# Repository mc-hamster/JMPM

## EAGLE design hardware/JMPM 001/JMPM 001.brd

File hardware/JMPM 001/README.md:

Sent to JLC PCB on May 7, 2020

Distributor part numbers for LCSC are included as an attribute on every component.

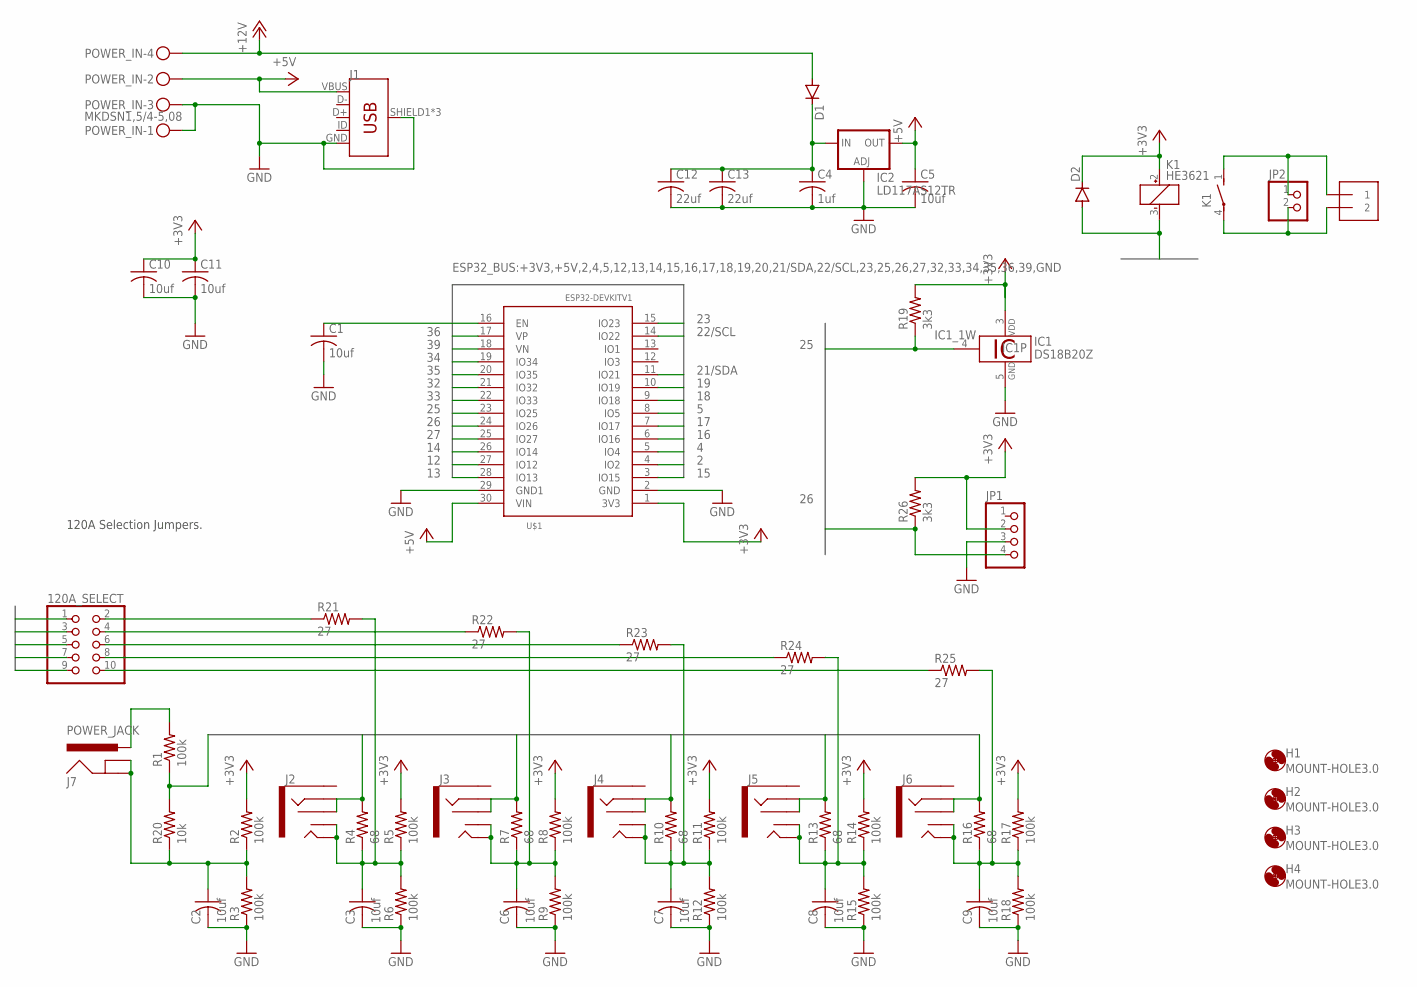
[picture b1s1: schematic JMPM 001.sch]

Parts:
120A_SELECT: PINHD-2X5; 2X05
C1, C2, C3, C5, C6, C7, C8, C9, C10, C11: 10uf; C0603; LCSC_PART_NUMBER C19702
C4: 1uf; C0603; LCSC_PART_NUMBER C15849
C12, C13: 22uf; C0805; LCSC_PART_NUMBER C45783
D1, D2: DIODE-DO-214AC; DO-214AC; LCSC_PART_NUMBER C95872
H1, H2, H3, H4: MOUNT-HOLE3.0; 3,0
IC1: DS18B20Z; SO08; LCSC_PART_NUMBER C97190
IC2: LD117AS12TR; SOT223; LCSC_PART_NUMBER C6187
J1: USB_MICRO-BREDUCED_PASTE; USB-B-MICRO-SMD_RED_PASTE
J2, J3, J4, J5, J6: AUDIO_JACK_3.5MM_KIT; AUDIO-JACK-KIT
J7: POWER_JACK; POWER_JACK_PTH
JP1: PINHD-1X4/90; 1X04/90
JP2: PINHD-1X2; 1X02
JP2B: 1X2-3.5MM; MPN OSTTE020161
K1: HE3621; MPN HE3621A0510
POWER_IN: MKDSN1,5/4-5,08
R1, R2, R3, R5, R6, R8, R9, R11, R12, R14, R15, R17, R18: 100k; R0603; LCSC_PART_NUMBER C25803
R4, R7, R10, R13, R16: 68; R0603; LCSC_PART_NUMBER C27592
R19, R26: 3k3; R0603; LCSC_PART_NUMBER C22978
R20: 10k; R0603; LCSC_PART_NUMBER C25804
R21, R22, R23, R24, R25: 27; R0603; LCSC_PART_NUMBER C25190
U$1: ESP32DEVKITV1; ESP32-DEVKITV1

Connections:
2: U$1.4 (IO2)
4: U$1.5 (IO4)
5: U$1.8 (IO5)
12: U$1.27 (IO12)
13: U$1.28 (IO13)
14: U$1.26 (IO14)
15: U$1.3 (IO15)
16: U$1.6 (IO16)
17: U$1.7 (IO17)
18: U$1.9 (IO18)
19: U$1.10 (IO19)
21/SDA: U$1.11 (IO21)
22/SCL: U$1.14 (IO22)
23: U$1.15 (IO23)
25: IC1.4 (1W), R19.1, U$1.23 (IO25)
26: JP1.4, R26.1, U$1.24 (IO26)
27: D2.A, K1.3 (-), U$1.25 (IO27)
32: 120A_SELECT.7, J5.RING, J5.RSH, R13.2, U$1.21 (IO32)
33: 120A_SELECT.9, J6.RING, J6.RSH, R16.2, U$1.22 (IO33)
34: 120A_SELECT.3, J3.RING, J3.RSH, R7.2, U$1.19 (IO34)
35: 120A_SELECT.5, J4.RING, J4.RSH, R10.2, U$1.20 (IO35)
36: R1.1, R20.2, U$1.17 (VP)
39: 120A_SELECT.1, J2.RING, J2.RSH, R4.2, U$1.18 (VN)
+3V3: C10.1, C11.1, D2.C, IC1.3 (VDD), JP1.2, K1.2 (+), R2.2, R5.2, R8.2, R11.2, R14.2, R17.2, R19.2, R26.2, U$1.1 (3V3)
+5V: C5.1, IC2.4 (OUT), J1.VBUS, POWER_IN.2, U$1.30 (VIN)
+12V: D1.A, POWER_IN.4
GND: C1.2, C2.2, C3.2, C4.2, C5.2, C6.2, C7.2, C8.2, C9.2, C10.2, C11.2, C12.2, C13.2, IC1.5 (GND), IC2.1 (ADJ), J1.GND, J1.SHIELD1 (SHIELD), J1.SHIELD2 (SHIELD), J1.SHIELD3 (SHIELD), JP1.3, POWER_IN.1, POWER_IN.3, R3.1, R6.1, R9.1, R12.1, R15.1, R18.1, U$1.2 (GND), U$1.29 (GND1)
unnamed: C1.1, U$1.16 (EN)
unnamed: C4.1, C12.1, C13.1, D1.C, IC2.3 (IN)
unnamed: J7.PWR, R1.2
unnamed: JP2.1, JP2B.1, K1.1 (S)
unnamed: 120A_SELECT.2, R21.1
unnamed: C2.1, J7.GND, J7.GNDBREAK, R2.1, R3.2, R20.1
unnamed: 120A_SELECT.4, R22.1
unnamed: C6.1, J3.TIP, J3.TSH, R7.1, R8.1, R9.2, R22.2
unnamed: 120A_SELECT.6, R23.1
unnamed: C7.1, J4.TIP, J4.TSH, R10.1, R11.1, R12.2, R23.2
unnamed: 120A_SELECT.8, R24.1
unnamed: C8.1, J5.TIP, J5.TSH, R13.1, R14.1, R15.2, R24.2
unnamed: 120A_SELECT.10, R25.1
unnamed: C9.1, J6.TIP, J6.TSH, R16.1, R17.1, R18.2, R25.2
unnamed: C3.1, J2.TIP, J2.TSH, R4.1, R5.1, R6.2, R21.2
unnamed: JP2.2, JP2B.2, K1.4

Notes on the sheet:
120A Selection Jumpers.

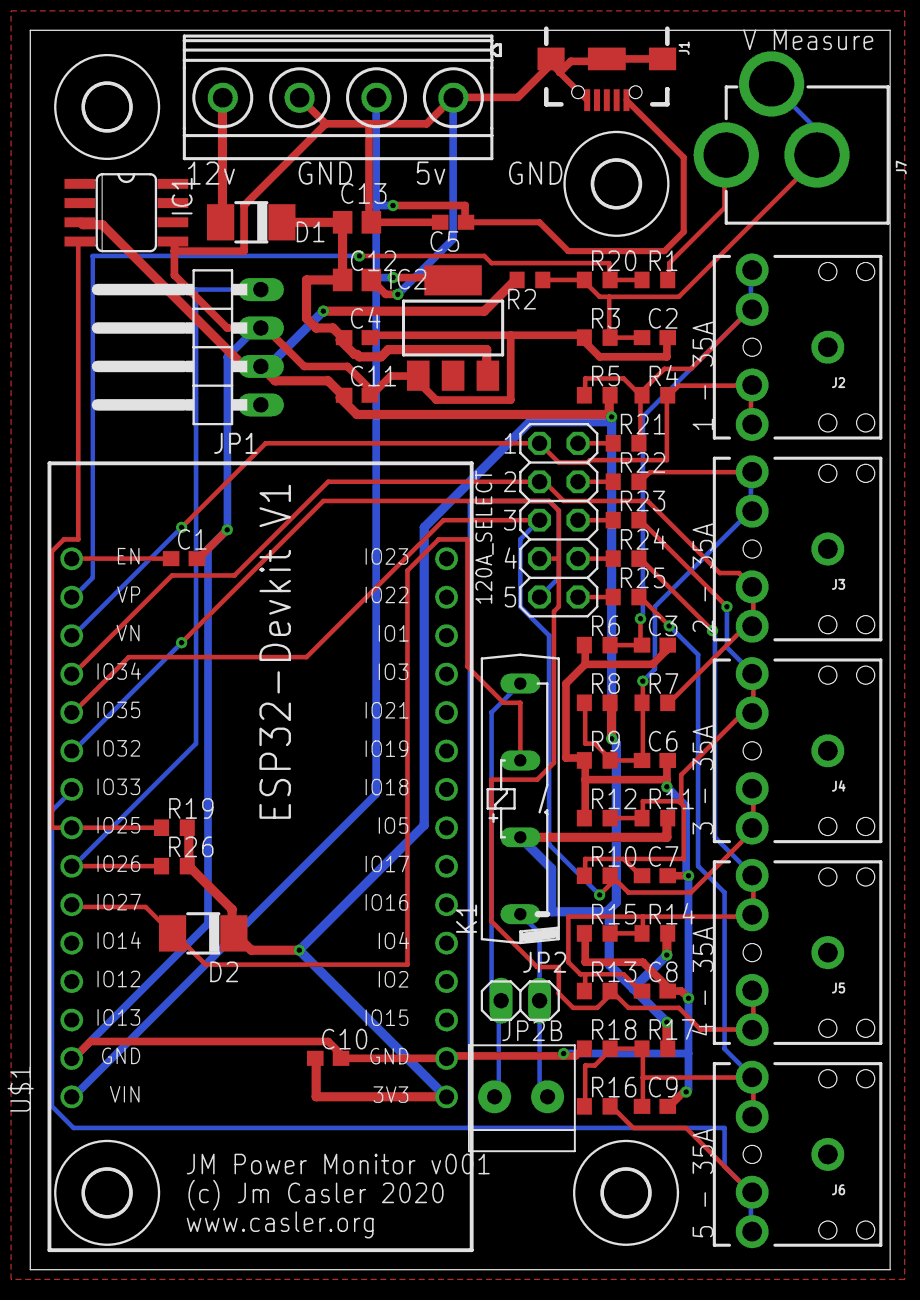
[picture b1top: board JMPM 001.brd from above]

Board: 2 copper layers, 56.8 x 81.9 mm, 61 parts (0 on the bottom side), 29 nets.

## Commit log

2020-05-17 Initial Checkin
2020-05-18 Created JSON interface to update the calibration.
    Also save calibration values as a preference in flash memory.
2020-05-23 Support for OTA updates.
2020-05-23 Support for http authentication
2020-05-25 Start to support emoncms as a target for data

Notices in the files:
parts and their libraries:
SparkFun-Connectors: Licensing: Creative Commons ShareAlike 4.0 International - https://creativecommons.org/licenses/by-sa/4.0
